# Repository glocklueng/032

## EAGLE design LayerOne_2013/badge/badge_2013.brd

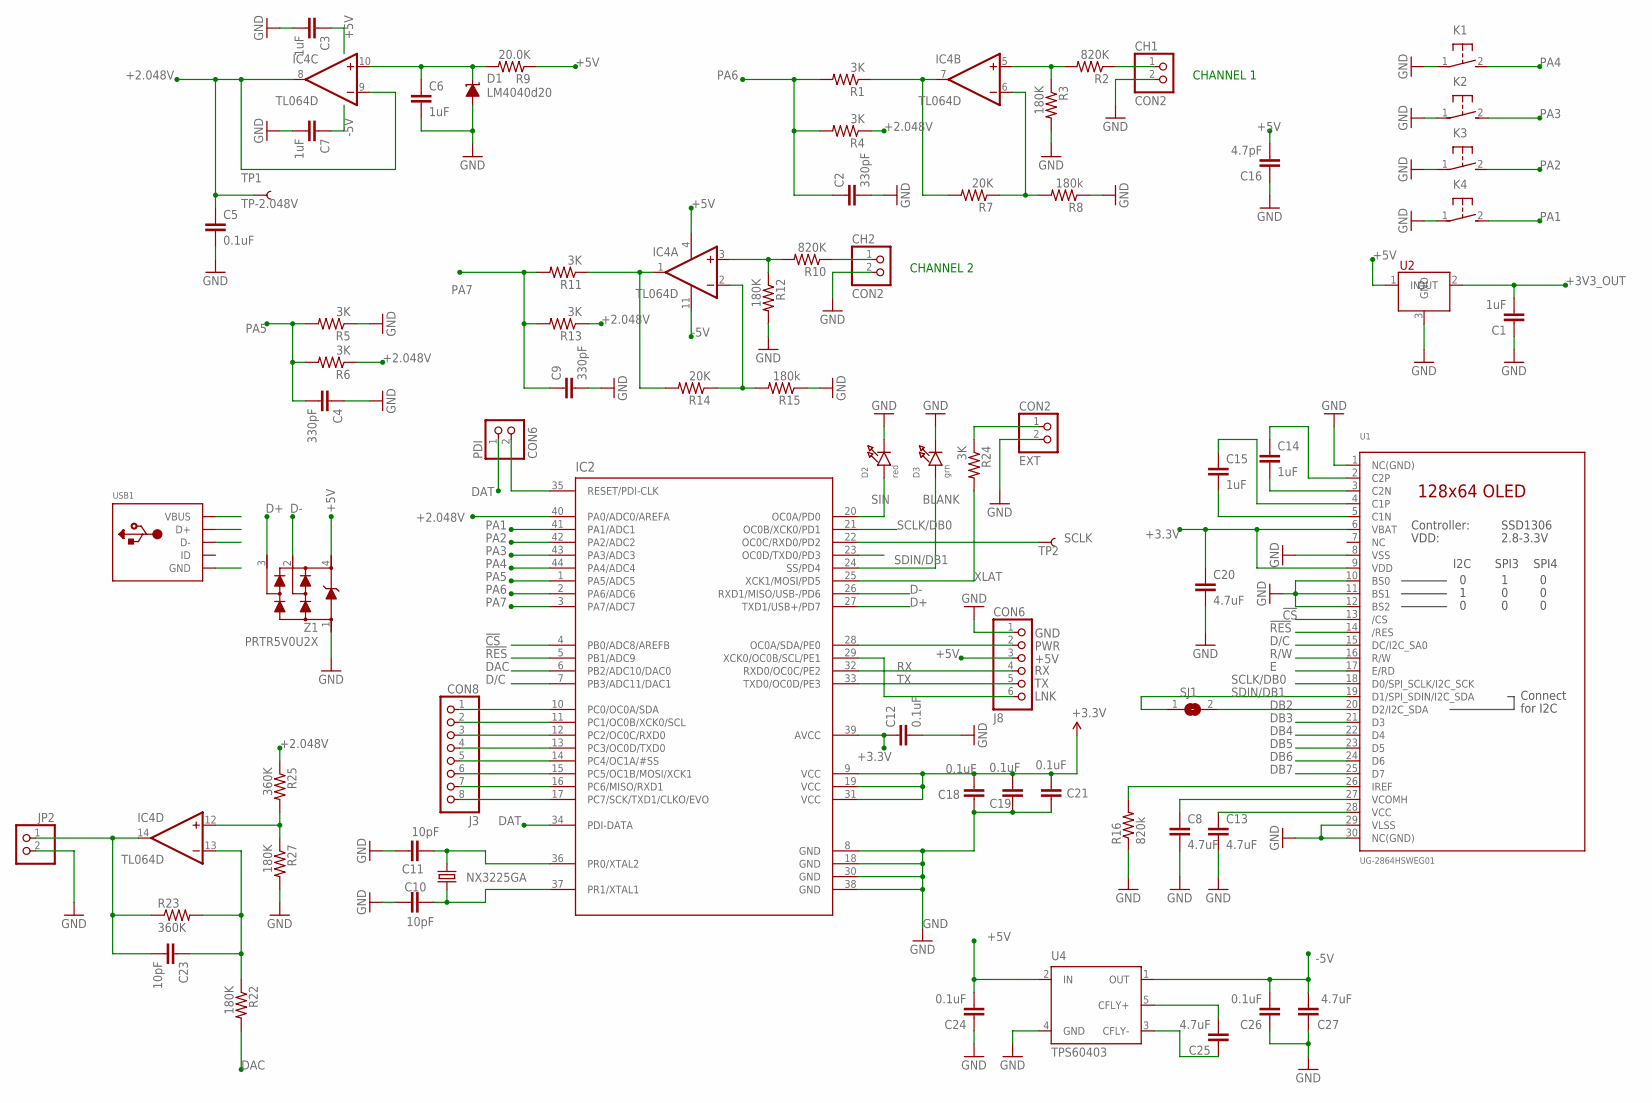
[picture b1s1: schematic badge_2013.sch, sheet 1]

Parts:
C1, C3, C6, C7, C14, C15: 1uF; 0805
C2, C4, C9: 330pF; 0805
C5, C12, C18, C19, C21, C24, C26: 0.1uF; 0805
C8, C13, C20, C25, C27: 4.7uF; 0805
C10, C11, C23: 10pF; 0805
C16: 4.7pF; 0805
CH1, CH2: CON2; 1X02_OVAL
CON2: EXT; 1X02_OVAL
CON6: J8; 1X06_OVAL
CON8: J3; 1X08_OVAL
D1: LM4040d20; DBZ_R-PDSO-G3
D2: red; CHIPLED_0805
D3: grn; CHIPLED_0805
IC2: NONOLITH_ATXMEGAXXA4U-AU; NONOLITH_TQFP-44
IC4: TL064D; SO14
JP2: HEADER-1X2; 1X02_OVAL
K1, K2, K3, K4: 5-XX; B3F-5XX
PDI: CON6; 1X02_OVAL
R1, R4, R5, R6, R11, R13, R24: 3K; R0805
R2, R10: 820K; R0805
R3, R12, R22, R27: 180K; R0805
R7, R14: 20K; R0805
R8, R15: 180k; R0805
R9: 20.0K; R0805
R16: 820k; R0805
R23, R25: 360K; R0805
SJ1: SOLDERJUMPERREFLOW; SOLDERJUMPER_REFLOW
TP1: TP-2.048V; PAD.02X.02
TP2: TEST-POINT2; PAD.02X.02
U1: UG-2864HSWEG01; MICROBUILDER_UG-2864HSWEG01_0.96IN_WRAPAROUND
U2: AP7333-33SOT23-3; SOT23-3
U4: TPS60403; SOT-23-5
USB1: USBMINIB; USB-MINIB
X2: NX3225GA
Z1: PRTR5V0U2X; SOT143B

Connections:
!CS: IC2.4 (PB0/ADC8/AREFB), U1.13 (/CS)
!RES: IC2.5 (PB1/ADC9), U1.14 (/RES)
+2.048V: C5.1, IC2.40 (PA0/ADC0/AREFA), IC4.8 (OUT), IC4.9 (-IN), R4.1, R6.1, R13.1, R25.1, TP1.P$1
+3.3V: C12.1, C18.2, C19.2, C20.1, C21.2, IC2.9 (VCC), IC2.19 (VCC), IC2.31 (VCC), IC2.39 (AVCC), U1.6 (VBAT), U1.9 (VDD); also elsewhere on the board
+3V3_OUT: C1.2, U2.2 (OUT); also elsewhere on the board
+5V: C3.1, C16.2, C24.2, CON6.3, IC4.4 (V+), R9.1, U2.1 (IN), U4.2 (IN), USB1.VBUS, Z1.4
-5V: C7.1, C26.2, C27.2, IC4.11 (V-), U4.1 (OUT)
BLANK: D3.A, IC2.24 (SS/PD4); also elsewhere on the board
D+: IC2.27 (TXD1/USB+/PD7), USB1.D+, Z1.3
D-: IC2.26 (RXD1/MISO/USB-/PD6), USB1.D-, Z1.2
D/C: IC2.7 (PB3/ADC11/DAC1), U1.15 (DC/I2C_SA0)
DAC: IC2.6 (PB2/ADC10/DAC0), R22.2
DAT: IC2.34 (PDI-DATA), PDI.1
DB2: SJ1.2, U1.20 (D2/I2C_SDA)
DB3: U1.21 (D3)
DB4: U1.22 (D4)
DB5: U1.23 (D5)
DB6: U1.24 (D6)
DB7: U1.25 (D7)
DGND: X2.2 (DGND), X2.4 (DGND)
E: U1.17 (E/RD)
GND: C1.1, C2.2, C3.2, C4.1, C5.2, C6.2, C7.2, C8.2, C9.2, C10.1, C11.1, C12.2, C13.2, C16.1, C18.1, C19.1, C20.2, C21.1, C24.1, C26.1, C27.1, CH1.2, CH2.2, CON2.2, CON6.1, D1.2 (A), D2.C, D3.C, IC2.8 (GND), IC2.18 (GND), IC2.30 (GND), IC2.38 (GND), JP2.2, K1.1, K2.1, K3.1, K4.1, R3.2, R5.1, R8.1, R12.2, R15.1, R16.1, R27.2, U1.1 (NC(GND)), U1.8 (VSS), U1.10 (BS0), U1.11 (BS1), U1.12 (BS2), U1.29 (VLSS), U1.30 (NC(GND)), U2.3 (GND), U4.4 (GND), USB1.GND, Z1.1; also elsewhere on the board
J3: CON8.5, IC2.14 (PC4/OC1A/#SS)
LNK: CON6.6, IC2.29 (XCK0/OC0B/SCL/PE1)
unnamed: C14.1, U1.2 (C2P)
unnamed: C14.2, U1.3 (C2N)
unnamed: C15.1, U1.4 (C1P)
unnamed: C15.2, U1.5 (C1N)
unnamed: CON2.1, R24.1
unnamed: C23.2, IC4.14 (OUT), JP2.1, R23.1
unnamed: C25.2, U4.5 (CFLY+)
unnamed: C25.1, U4.3 (CFLY-)
unnamed: CON8.1, IC2.10 (PC0/OC0A/SDA)
unnamed: CON8.2, IC2.11 (PC1/OC0B/XCK0/SCL)
unnamed: CON8.3, IC2.12 (PC2/OC0C/RXD0)
unnamed: CON8.4, IC2.13 (PC3/OC0D/TXD0)
unnamed: CON8.6, IC2.15 (PC5/OC1B/MOSI/XCK1)
unnamed: CON8.7, IC2.16 (PC6/MISO/RXD1)
unnamed: CON8.8, IC2.17 (PC7/SCK/TXD1/CLKO/EVO)
unnamed: IC4.12 (+IN), R25.2, R27.1
unnamed: C6.1, D1.1 (C), IC4.10 (+IN), R9.2
unnamed: C23.1, IC4.13 (-IN), R22.1, R23.2
unnamed: IC4.5 (+IN), R2.2, R3.1
unnamed: CH1.1, R2.1
unnamed: IC4.3 (+IN), R10.2, R12.1
unnamed: IC4.6 (-IN), R7.1, R8.2
unnamed: IC4.7 (OUT), R1.1, R7.2
unnamed: CH2.1, R10.1
unnamed: IC4.2 (-IN), R14.1, R15.2
unnamed: R16.2, U1.26 (IREF)
unnamed: C8.1, U1.27 (VCOMH)
unnamed: C13.1, U1.28 (VCC)
unnamed: IC4.1 (OUT), R11.1, R14.2
unnamed: C11.2, IC2.36 (PR0/XTAL2), X2.3 (2)
unnamed: C10.2, IC2.37 (PR1/XTAL1), X2.1
unnamed: IC2.35 (RESET/PDI-CLK), PDI.2
PA1: IC2.41 (PA1/ADC1), K4.2 (S)
PA2: IC2.42 (PA2/ADC2), K3.2 (S)
PA3: IC2.43 (PA3/ADC3), K2.2 (S)
PA4: IC2.44 (PA4/ADC4), K1.2 (S)
PA5: C4.2, IC2.1 (PA5/ADC5), R5.2, R6.2
PA6: C2.1, IC2.2 (PA6/ADC6), R1.2, R4.2
PA7: C9.1, IC2.3 (PA7/ADC7), R11.2, R13.2
PWR: CON6.2, IC2.28 (OC0A/SDA/PE0)
R/W: U1.16 (R/W)
RX: CON6.4, IC2.32 (RXD0/OC0C/PE2)
SCLK: IC2.22 (OC0C/RXD0/PD2), TP2.P$1; also elsewhere on the board
SCLK/DB0: IC2.21 (OC0B/XCK0/PD1), U1.18 (D0/SPI_SCLK/I2C_SCK)
SDIN/DB1: IC2.23 (OC0D/TXD0/PD3), SJ1.1, U1.19 (D1/SPI_SDIN/I2C_SDA)
SIN: D2.A, IC2.20 (OC0A/PD0); also elsewhere on the board
TX: CON6.5, IC2.33 (TXD0/OC0D/PE3)
XLAT: IC2.25 (XCK1/MOSI/PD5), R24.2; also elsewhere on the board

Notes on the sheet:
CHANNEL 1
CHANNEL 2

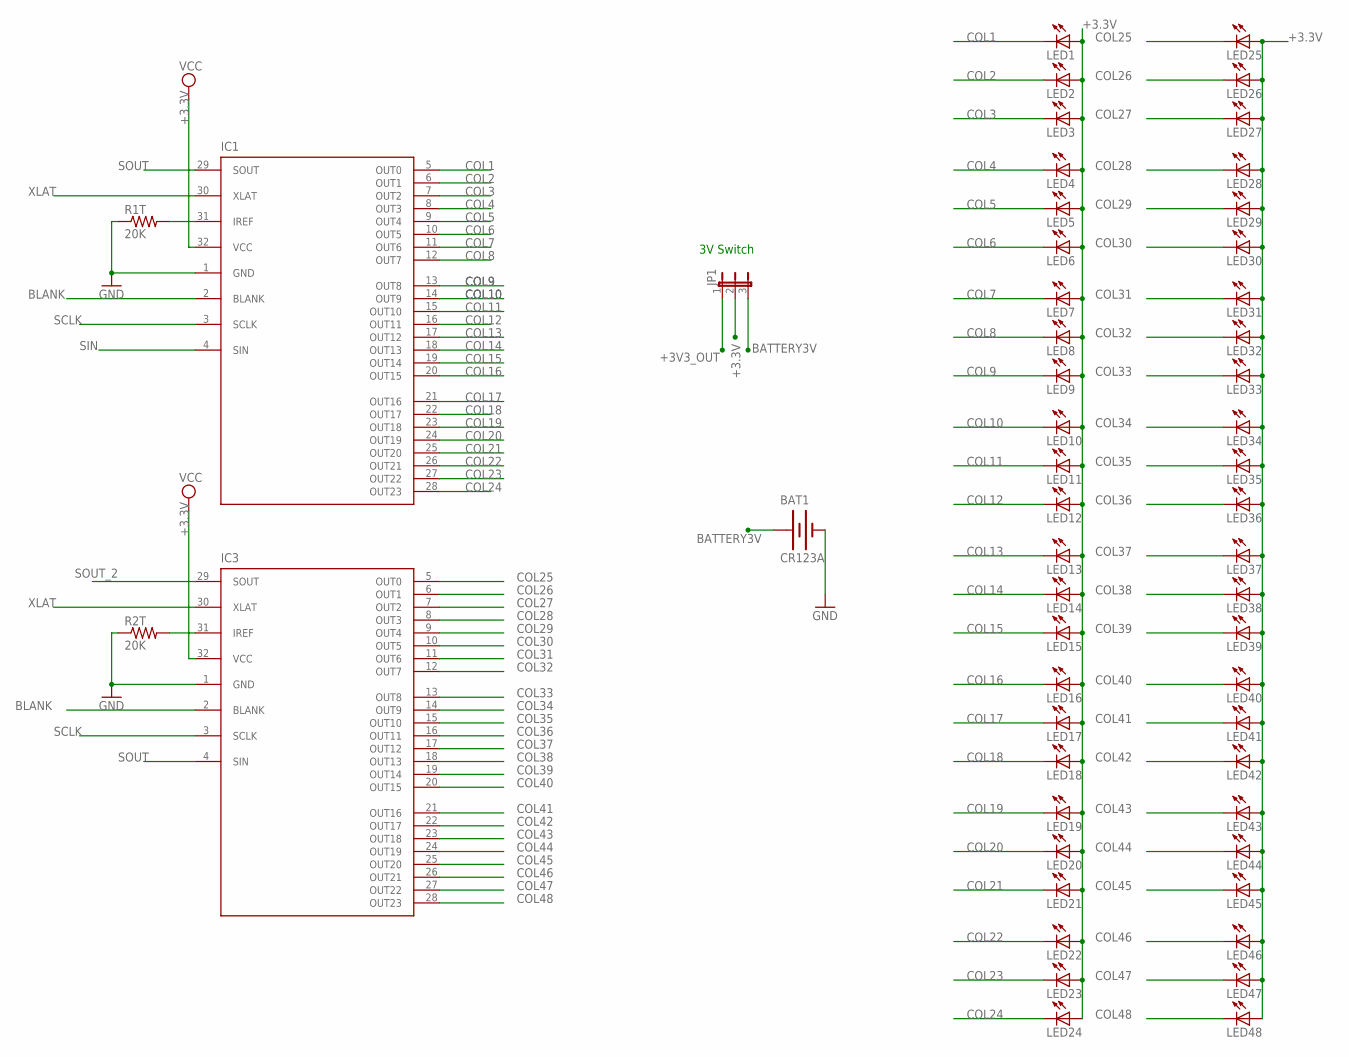
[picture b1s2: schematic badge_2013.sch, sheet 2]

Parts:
BAT1: CR123A; BATTERY_CR123A
IC1, IC3: SLICE_NOSHIFT_TLC5947HTSSOP32DAP; HTSSOP32DAP
JP1: JUMPER3
LED1, LED2, LED3, LED4, LED5, LED6, LED7, LED8, LED9, LED10, LED11, LED12, LED13, LED14, LED15, LED16, LED17, LED18, LED19, LED20, LED21, LED22, LED23, LED24, LED25, LED26, LED27, LED28, LED29, LED30, LED31, LED32, LED33, LED34, LED35, LED36, LED37, LED38, LED39, LED40, LED41, LED42, LED43, LED44, LED45, LED46, LED47, LED48: LED3MM
R1T, R2T: 20K; R0805

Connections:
+3.3V: IC1.32 (VCC), IC3.32 (VCC), JP1.2, LED1.A, LED2.A, LED3.A, LED4.A, LED5.A, LED6.A, LED7.A, LED8.A, LED9.A, LED10.A, LED11.A, LED12.A, LED13.A, LED14.A, LED15.A, LED16.A, LED17.A, LED18.A, LED19.A, LED20.A, LED21.A, LED22.A, LED23.A, LED24.A, LED25.A, LED26.A, LED27.A, LED28.A, LED29.A, LED30.A, LED31.A, LED32.A, LED33.A, LED34.A, LED35.A, LED36.A, LED37.A, LED38.A, LED39.A, LED40.A, LED41.A, LED42.A, LED43.A, LED44.A, LED45.A, LED46.A, LED47.A, LED48.A; also elsewhere on the board
+3V3_OUT: JP1.1; also elsewhere on the board
BATTERY3V: BAT1.+, JP1.3
BLANK: IC1.2 (BLANK), IC3.2 (BLANK); also elsewhere on the board
COL1: IC1.5 (OUT0), LED1.K (C)
COL2: IC1.6 (OUT1), LED2.K (C)
COL3: IC1.7 (OUT2), LED3.K (C)
COL4: IC1.8 (OUT3), LED4.K (C)
COL5: IC1.9 (OUT4), LED5.K (C)
COL6: IC1.10 (OUT5), LED6.K (C)
COL7: IC1.11 (OUT6), LED7.K (C)
COL8: IC1.12 (OUT7), LED8.K (C)
COL9: IC1.13 (OUT8), LED9.K (C)
COL10: IC1.14 (OUT9), LED10.K (C)
COL11: IC1.15 (OUT10), LED11.K (C)
COL12: IC1.16 (OUT11), LED12.K (C)
COL13: IC1.17 (OUT12), LED13.K (C)
COL14: IC1.18 (OUT13), LED14.K (C)
COL15: IC1.19 (OUT14), LED15.K (C)
COL16: IC1.20 (OUT15), LED16.K (C)
COL17: IC1.21 (OUT16), LED17.K (C)
COL18: IC1.22 (OUT17), LED18.K (C)
COL19: IC1.23 (OUT18), LED19.K (C)
COL20: IC1.24 (OUT19), LED20.K (C)
COL21: IC1.25 (OUT20), LED21.K (C)
COL22: IC1.26 (OUT21), LED22.K (C)
COL23: IC1.27 (OUT22), LED23.K (C)
COL24: IC1.28 (OUT23), LED24.K (C)
COL25: IC3.5 (OUT0), LED25.K (C)
COL26: IC3.6 (OUT1), LED26.K (C)
COL27: IC3.7 (OUT2), LED27.K (C)
COL28: IC3.8 (OUT3), LED28.K (C)
COL29: IC3.9 (OUT4), LED29.K (C)
COL30: IC3.10 (OUT5), LED30.K (C)
COL31: IC3.11 (OUT6), LED31.K (C)
COL32: IC3.12 (OUT7), LED32.K (C)
COL33: IC3.13 (OUT8), LED33.K (C)
COL34: IC3.14 (OUT9), LED34.K (C)
COL35: IC3.15 (OUT10), LED35.K (C)
COL36: IC3.16 (OUT11), LED36.K (C)
COL37: IC3.17 (OUT12), LED37.K (C)
COL38: IC3.18 (OUT13), LED38.K (C)
COL39: IC3.19 (OUT14), LED39.K (C)
COL40: IC3.20 (OUT15), LED40.K (C)
COL41: IC3.21 (OUT16), LED41.K (C)
COL42: IC3.22 (OUT17), LED42.K (C)
COL43: IC3.23 (OUT18), LED43.K (C)
COL44: IC3.24 (OUT19), LED44.K (C)
COL45: IC3.25 (OUT20), LED45.K (C)
COL46: IC3.26 (OUT21), LED46.K (C)
COL47: IC3.27 (OUT22), LED47.K (C)
COL48: IC3.28 (OUT23), LED48.K (C)
GND: BAT1.-, IC1.1 (GND), IC3.1 (GND), R1T.1, R2T.1; also elsewhere on the board
unnamed: IC3.31 (IREF), R2T.2
unnamed: IC1.31 (IREF), R1T.2
SCLK: IC1.3 (SCLK), IC3.3 (SCLK); also elsewhere on the board
SIN: IC1.4 (SIN); also elsewhere on the board
SOUT: IC1.29 (SOUT), IC3.4 (SIN)
SOUT_2: IC3.29 (SOUT)
XLAT: IC1.30 (XLAT), IC3.30 (XLAT); also elsewhere on the board

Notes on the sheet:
3V Switch

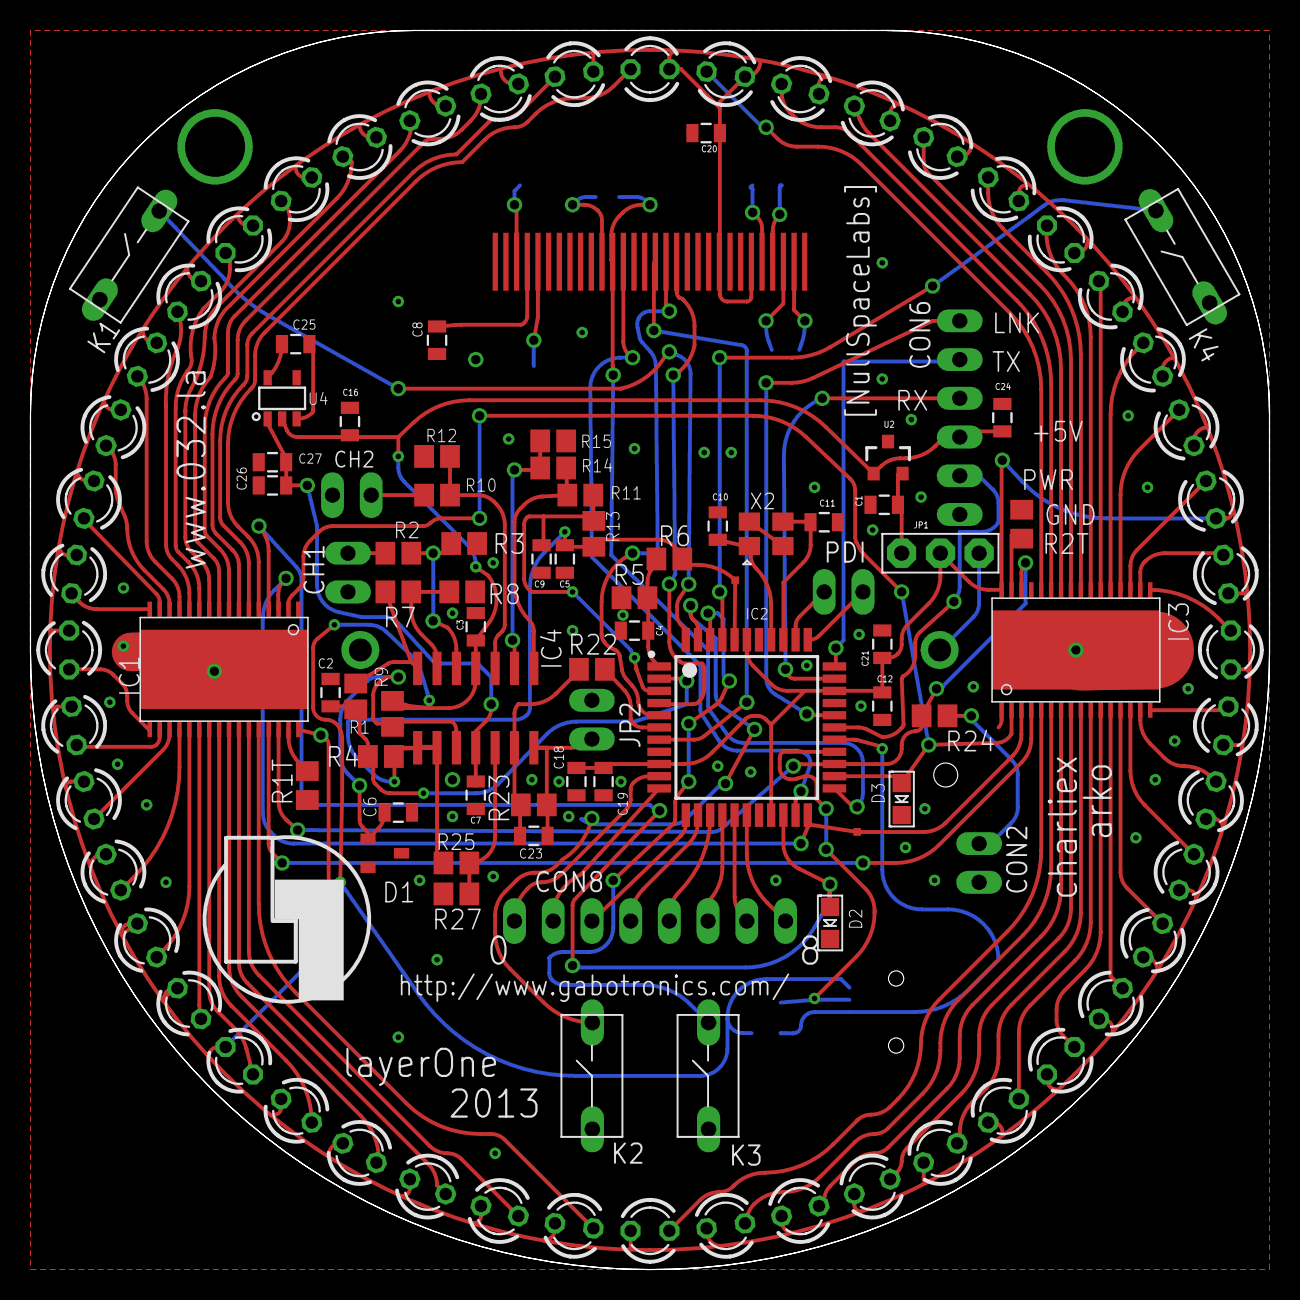
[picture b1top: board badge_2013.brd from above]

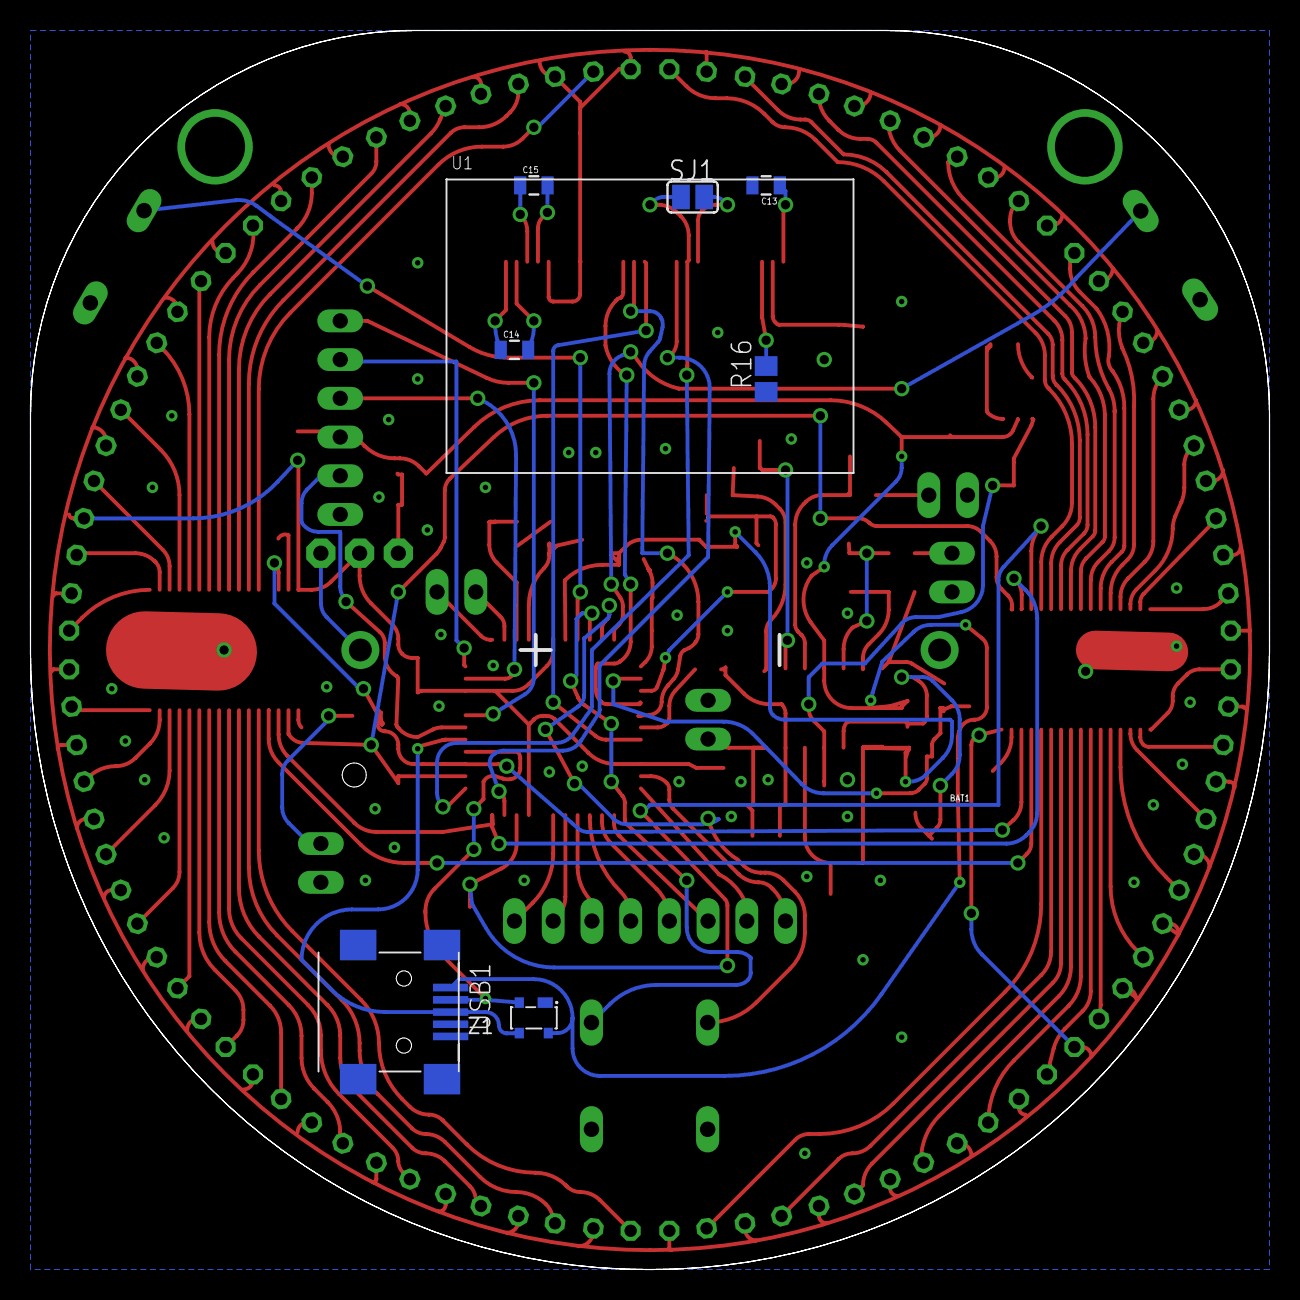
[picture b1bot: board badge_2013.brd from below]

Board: 2 copper layers, 81.3 x 81.3 mm, 125 parts (9 on the bottom side), 117 nets.

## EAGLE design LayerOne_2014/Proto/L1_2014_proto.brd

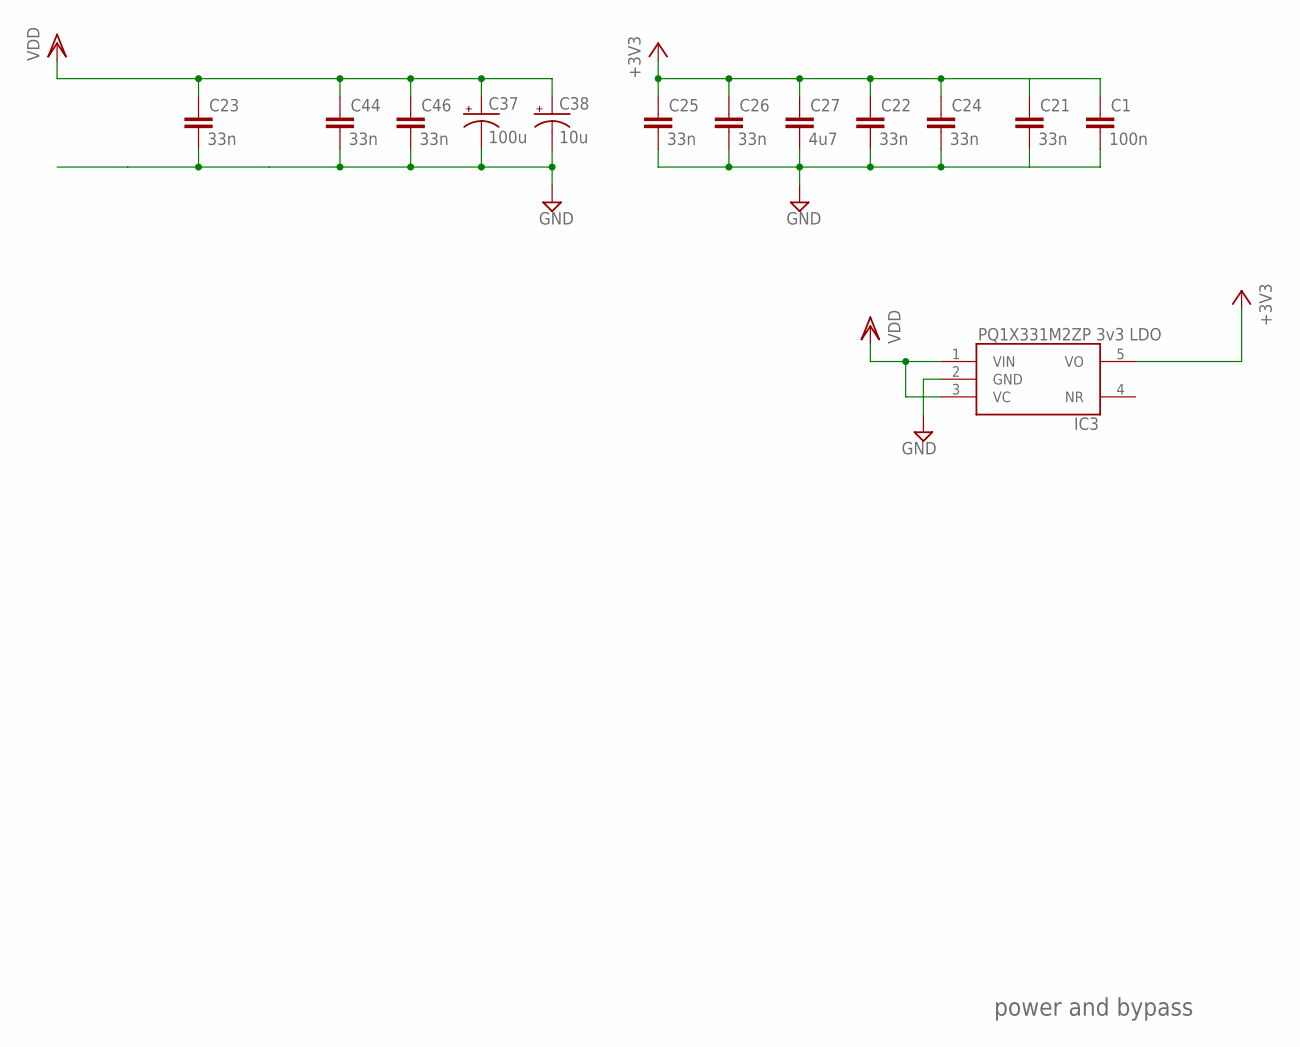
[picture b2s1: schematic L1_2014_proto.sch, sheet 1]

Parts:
C1: 100n; RLC_0603
C21, C22, C23, C24, C25, C26, C44, C46: 33n; RLC_0603
C27: 4u7; RLC_1210
C37: 100u; CAPCAITOR-ELECTROLYTIC-ALCHIP-MZA-F80
C38: 10u; CAPCAITOR-ELECTROLYTIC-ALCHIP-MZA-F80
IC3: PQ1X331M2ZP-3V3-LDO-SOT-23-5; SOT-23-5

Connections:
+3V3: C1.1, C21.1, C22.1, C24.1, C25.1, C26.1, C27.1, IC3.5 (VO); also elsewhere on the board
GND: C1.2, C21.2, C22.2, C23.2, C24.2, C25.2, C26.2, C27.2, C37.-, C38.-, C44.2, C46.2, IC3.2 (GND); also elsewhere on the board
VDD: C23.1, C37.+, C38.+, C44.1, C46.1, IC3.1 (VIN), IC3.3 (VC); also elsewhere on the board

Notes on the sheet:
power and bypass

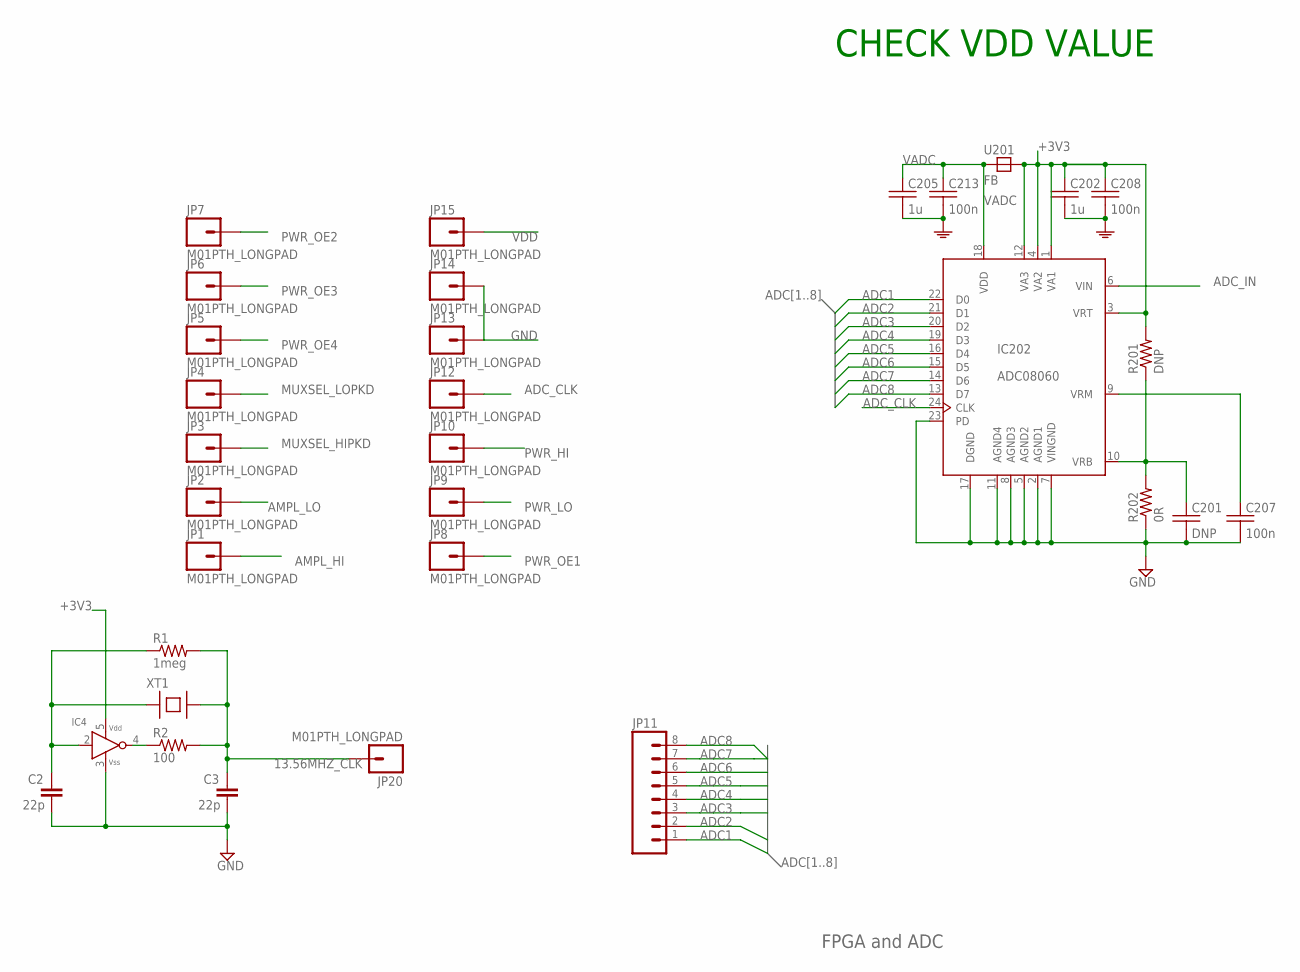
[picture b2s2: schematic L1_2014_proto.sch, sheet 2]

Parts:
C2, C3: 22p; RLC_0603
C201: DNP; 0603
C202, C205: 1u; 0603
C207, C208, C213: 100n; 0603
IC4: HCU-INVERTER; SMV-5
IC202: ADC08060; TSSOP24
JP1, JP2, JP3, JP4, JP5, JP6, JP7, JP8, JP9, JP10, JP12, JP13, JP14, JP15, JP20: M01PTH_LONGPAD; 1X01_LONGPAD
JP11: M08LONGPADS; 1X08_LONGPADS
R1: 1meg; RLC_0603
R2: 100; RLC_0603
R201: DNP; 0603
R202: 0R; 0603
U201: FB; 0805
XT1: XTAL-SMD-CITIZEN-CS10

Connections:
13.56MHZ_CLK: C3.1, JP20.1, R1.2, R2.2, XT1.B
+3V3: C202.1, C208.1, IC4.5 (VDD), IC202.1 (VA1), IC202.3 (VRT), IC202.4 (VA2), IC202.12 (VA3), R201.2, U201.2 (B); also elsewhere on the board
ADC1: IC202.22 (D0), JP11.1; also elsewhere on the board
ADC2: IC202.21 (D1), JP11.2; also elsewhere on the board
ADC3: IC202.20 (D2), JP11.3; also elsewhere on the board
ADC4: IC202.19 (D3), JP11.4; also elsewhere on the board
ADC5: IC202.16 (D4), JP11.5; also elsewhere on the board
ADC6: IC202.15 (D5), JP11.6; also elsewhere on the board
ADC7: IC202.14 (D6), JP11.7; also elsewhere on the board
ADC8: IC202.13 (D7), JP11.8; also elsewhere on the board
ADC_CLK: IC202.24 (CLK), JP12.1; also elsewhere on the board
ADC_IN: IC202.6 (VIN); also elsewhere on the board
AMPL_HI: JP1.1; also elsewhere on the board
AMPL_LO: JP2.1; also elsewhere on the board
GND: C2.2, C3.2, C201.2, C202.2, C205.2, C207.2, C208.2, C213.2, IC4.3 (VSS), IC202.2 (AGND1), IC202.5 (AGND2), IC202.7 (VINGND), IC202.8 (AGND3), IC202.11 (AGND4), IC202.17 (DGND), IC202.23 (PD), JP13.1, JP14.1, R202.1; also elsewhere on the board
MUXSEL_HIPKD: JP3.1; also elsewhere on the board
MUXSEL_LOPKD: JP4.1; also elsewhere on the board
unnamed: IC4.4 (Y), R2.1
unnamed: C2.1, IC4.2 (A), R1.1, XT1.A
unnamed: C201.1, IC202.10 (VRB), R201.1, R202.2
unnamed: C207.1, IC202.9 (VRM)
PWR_HI: JP10.1; also elsewhere on the board
PWR_LO: JP9.1; also elsewhere on the board
PWR_OE1: JP8.1; also elsewhere on the board
PWR_OE2: JP7.1; also elsewhere on the board
PWR_OE3: JP6.1; also elsewhere on the board
PWR_OE4: JP5.1; also elsewhere on the board
VADC: C205.1, C213.1, IC202.18 (VDD), U201.1 (A)
VDD: JP15.1; also elsewhere on the board

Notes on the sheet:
FPGA and ADC
CHECK VDD VALUE

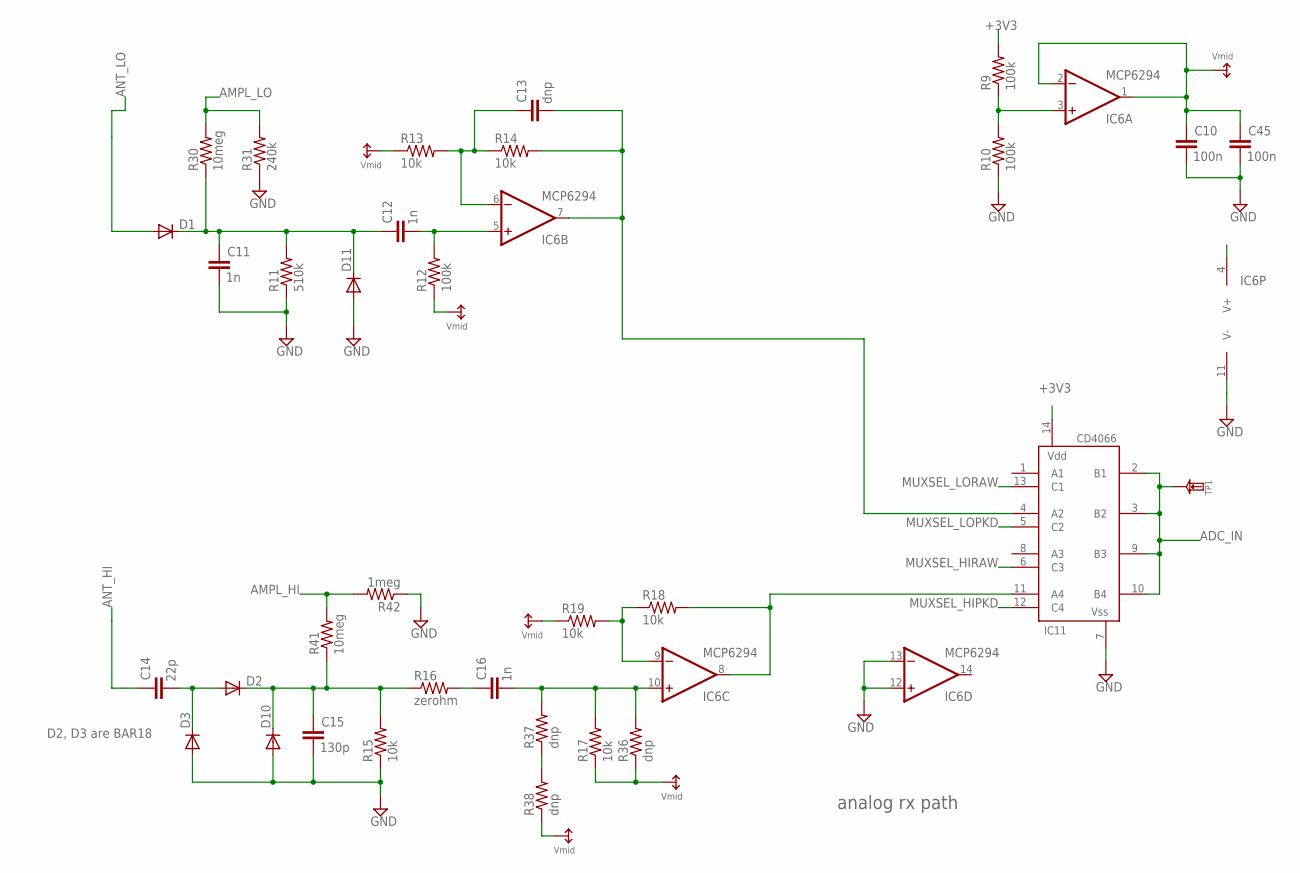
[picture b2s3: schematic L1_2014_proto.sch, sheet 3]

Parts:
C10, C45: 100n; RLC_0603
C11, C12, C16: 1n; RLC_0603
C13: dnp; RLC_0603
C14: 22p; RLC_0603
C15: 130p; RLC_0603
D1, D2, D3, D10, D11: DIODE-SMD-SOT23; SOT23-3LEAD
IC6: MCP6294; TSSOP-14
IC11: CD4066; TSSOP-14
R9, R10, R12: 100k; RLC_0603
R11: 510k; RLC_0603
R13, R14, R15, R17, R18, R19: 10k; RLC_0603
R16: zerohm; RLC_0603
R30, R41: 10meg; RLC_0603
R31: 240k; RLC_0603
R36, R37, R38: dnp; RLC_0603
R42: 1meg; RLC_0603
TP1: TESTPADKEYSTONE-SMD; KEYSTONE-SMD-TESTPOINT-5015

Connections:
+3V3: IC6.4 (V+), IC11.14 (VDD), R9.2; also elsewhere on the board
ADCDR_HI: IC6.8 (OUT), IC11.11 (A4), R18.2
ADCDR_LO: C13.2, IC6.7 (OUT), IC11.4 (A2), R14.2
ADC_IN: IC11.2 (B1), IC11.3 (B2), IC11.9 (B3), IC11.10 (B4), TP1.1; also elsewhere on the board
AMPL_HI: R41.2, R42.2; also elsewhere on the board
AMPL_LO: R30.2, R31.2; also elsewhere on the board
ANT_HI: C14.1; also elsewhere on the board
ANT_LO: D1.1 (A); also elsewhere on the board
GND: C10.2, C11.2, C15.2, C45.2, D3.1 (A), D10.1 (A), D11.1 (A), IC6.11 (V-), IC6.12 (+IN), IC6.13 (-IN), IC11.7 (VSS), R10.1, R11.1, R15.1, R31.1, R42.1; also elsewhere on the board
MUXSEL_HIPKD: IC11.12 (C4); also elsewhere on the board
MUXSEL_HIRAW: IC11.6 (C3)
MUXSEL_LOPKD: IC11.5 (C2); also elsewhere on the board
MUXSEL_LORAW: IC11.13 (C1)
unnamed: IC6.3 (+IN), R9.1, R10.2
unnamed: IC6.9 (-IN), R18.1, R19.2
unnamed: C12.2, IC6.5 (+IN), R12.2
unnamed: C13.1, IC6.6 (-IN), R13.2, R14.1
unnamed: C16.1, R16.2
unnamed: C11.1, C12.1, D1.3 (C), D11.3 (C), R11.2, R30.1
unnamed: C14.2, D2.1 (A), D3.3 (C)
unnamed: C15.1, D2.3 (C), D10.3 (C), R15.2, R16.1, R41.1
unnamed: C16.2, IC6.10 (+IN), R17.2, R36.2, R37.2
unnamed: R37.1, R38.2
VMID: C10.1, C45.1, IC6.1 (OUT), IC6.2 (-IN), R12.1, R13.1, R17.1, R19.1, R36.1, R38.1

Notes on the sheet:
analog rx path
D2, D3 are BAR18

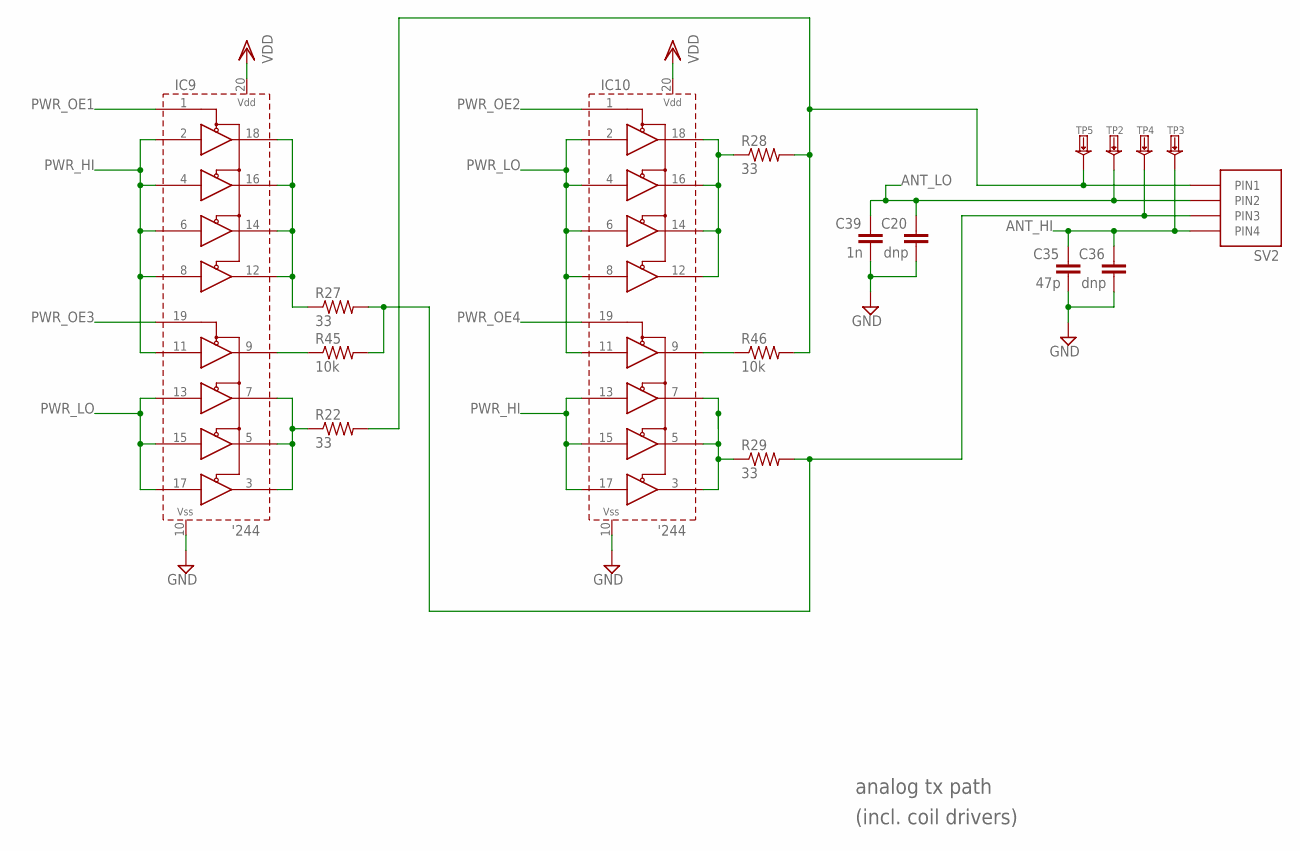
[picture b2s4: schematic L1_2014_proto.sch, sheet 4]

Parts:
C20, C36: dnp; RLC_0603
C35: 47p; RLC_0603
C39: 1n; RLC_0603
IC9, IC10: 74XX244-OCTAL-TRISTATE-BUFFERS; TSSOP-20
R22, R27, R28, R29: 33; RLC_0603
R45, R46: 10k; RLC_0603
SV2: HIROSE-MQ172-4POS
TP2, TP3, TP4, TP5: TESTPADKEYSTONE-SMD; KEYSTONE-SMD-TESTPOINT-5015

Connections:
ANT_HI: C35.1, C36.1, SV2.4 (PIN4), TP3.1; also elsewhere on the board
ANT_LO: C20.1, C39.1, SV2.2 (PIN2), TP2.1; also elsewhere on the board
GND: C20.2, C35.2, C36.2, C39.2, IC9.10 (VSS), IC10.10 (VSS); also elsewhere on the board
unnamed: R27.2, R29.2, R45.2, SV2.3 (PIN3), TP4.1
unnamed: R22.2, R28.2, R46.2, SV2.1 (PIN1), TP5.1
unnamed: IC9.12 (1Y4), IC9.14 (1Y3), IC9.16 (1Y2), IC9.18 (1Y1), R27.1
unnamed: IC10.12 (1Y4), IC10.14 (1Y3), IC10.16 (1Y2), IC10.18 (1Y1), R28.1
unnamed: IC9.3 (2Y4), IC9.5 (2Y3), IC9.7 (2Y2), R22.1
unnamed: IC10.3 (2Y4), IC10.5 (2Y3), IC10.7 (2Y2), R29.1
unnamed: IC9.9 (2Y1), R45.1
unnamed: IC10.9 (2Y1), R46.1
PWR_HI: IC9.2 (1A1), IC9.4 (1A2), IC9.6 (1A3), IC9.8 (1A4), IC9.11 (2A1), IC10.13 (2A2), IC10.15 (2A3), IC10.17 (2A4); also elsewhere on the board
PWR_LO: IC9.13 (2A2), IC9.15 (2A3), IC9.17 (2A4), IC10.2 (1A1), IC10.4 (1A2), IC10.6 (1A3), IC10.8 (1A4), IC10.11 (2A1); also elsewhere on the board
PWR_OE1: IC9.1 (1NOE); also elsewhere on the board
PWR_OE2: IC10.1 (1NOE); also elsewhere on the board
PWR_OE3: IC9.19 (2NOE); also elsewhere on the board
PWR_OE4: IC10.19 (2NOE); also elsewhere on the board
VDD: IC9.20 (VDD), IC10.20 (VDD); also elsewhere on the board

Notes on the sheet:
analog tx path
(incl. coil drivers)

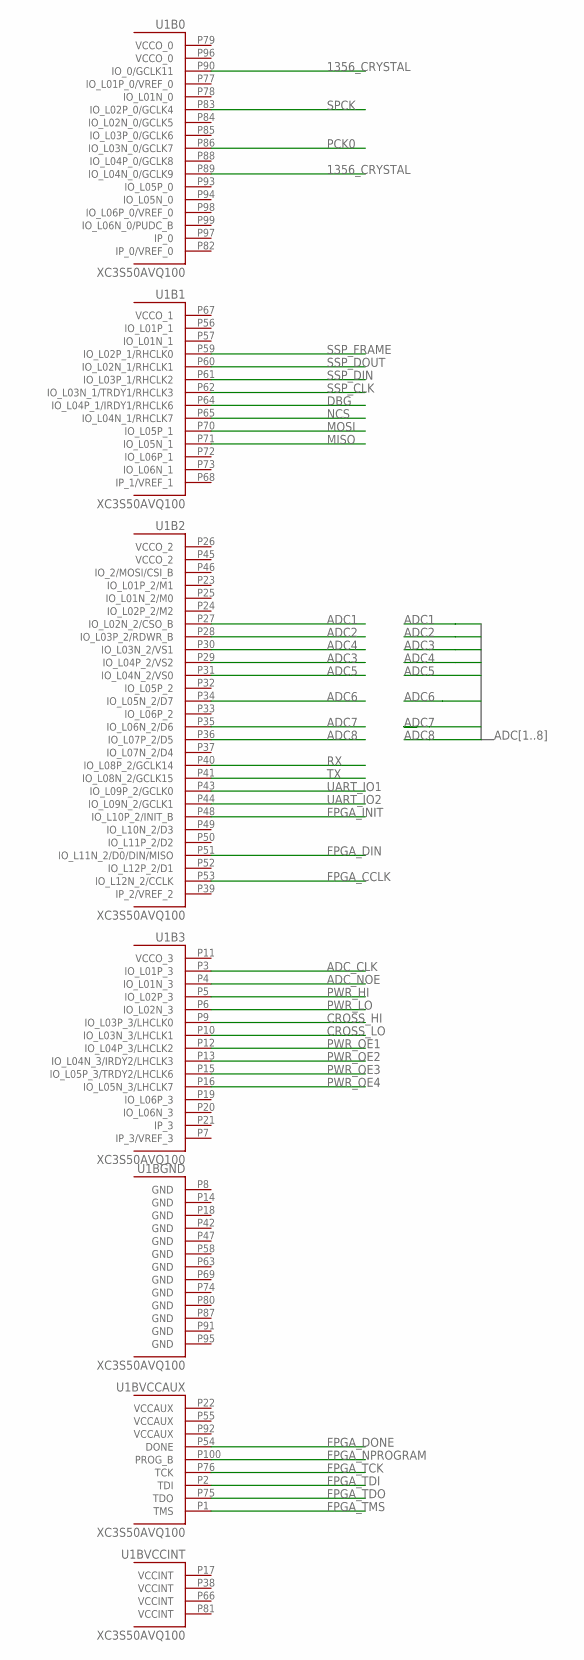
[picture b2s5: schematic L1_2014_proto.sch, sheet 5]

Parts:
U1: XC3S50AVQ100; VQ100

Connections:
1356_CRYSTAL: U1.P89 (IO_L04N_0/GCLK9), U1.P90 (IO_0/GCLK11)
ADC1: U1.P27 (IO_L02N_2/CSO_B); also elsewhere on the board
ADC2: U1.P28 (IO_L03P_2/RDWR_B); also elsewhere on the board
ADC3: U1.P29 (IO_L04P_2/VS2); also elsewhere on the board
ADC4: U1.P30 (IO_L03N_2/VS1); also elsewhere on the board
ADC5: U1.P31 (IO_L04N_2/VS0); also elsewhere on the board
ADC6: U1.P34 (IO_L05N_2/D7); also elsewhere on the board
ADC7: U1.P35 (IO_L06N_2/D6); also elsewhere on the board
ADC8: U1.P36 (IO_L07P_2/D5); also elsewhere on the board
ADC_CLK: U1.P3 (IO_L01P_3); also elsewhere on the board
ADC_NOE: U1.P4 (IO_L01N_3)
CROSS_HI: U1.P9 (IO_L03P_3/LHCLK0)
CROSS_LO: U1.P10 (IO_L03N_3/LHCLK1)
DBG: U1.P64 (IO_L04P_1/IRDY1/RHCLK6)
FPGA_CCLK: U1.P53 (IO_L12N_2/CCLK)
FPGA_DIN: U1.P51 (IO_L11N_2/D0/DIN/MISO)
FPGA_DONE: U1.P54 (DONE)
FPGA_INIT: U1.P48 (IO_L10P_2/INIT_B)
FPGA_NPROGRAM: U1.P100 (PROG_B)
FPGA_TCK: U1.P76 (TCK)
FPGA_TDI: U1.P2 (TDI)
FPGA_TDO: U1.P75 (TDO)
FPGA_TMS: U1.P1 (TMS)
GND: U1.P8 (GND), U1.P14 (GND), U1.P18 (GND), U1.P42 (GND), U1.P47 (GND), U1.P58 (GND), U1.P63 (GND), U1.P69 (GND), U1.P74 (GND), U1.P80 (GND), U1.P87 (GND), U1.P91 (GND), U1.P95 (GND); also elsewhere on the board
MISO: U1.P71 (IO_L05N_1)
MOSI: U1.P70 (IO_L05P_1)
NCS: U1.P65 (IO_L04N_1/RHCLK7)
PCK0: U1.P86 (IO_L03N_0/GCLK7)
PWR_HI: U1.P5 (IO_L02P_3); also elsewhere on the board
PWR_LO: U1.P6 (IO_L02N_3); also elsewhere on the board
PWR_OE1: U1.P12 (IO_L04P_3/LHCLK2); also elsewhere on the board
PWR_OE2: U1.P13 (IO_L04N_3/IRDY2/LHCLK3); also elsewhere on the board
PWR_OE3: U1.P15 (IO_L05P_3/TRDY2/LHCLK6); also elsewhere on the board
PWR_OE4: U1.P16 (IO_L05N_3/LHCLK7); also elsewhere on the board
RX: U1.P40 (IO_L08P_2/GCLK14)
SPCK: U1.P83 (IO_L02P_0/GCLK4)
SSP_CLK: U1.P62 (IO_L03N_1/TRDY1/RHCLK3)
SSP_DIN: U1.P61 (IO_L03P_1/RHCLK2)
SSP_DOUT: U1.P60 (IO_L02N_1/RHCLK1)
SSP_FRAME: U1.P59 (IO_L02P_1/RHCLK0)
TX: U1.P41 (IO_L08N_2/GCLK15)
UART_IO1: U1.P43 (IO_L09P_2/GCLK0)
UART_IO2: U1.P44 (IO_L09N_2/GCLK1)

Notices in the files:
parts and their libraries:
SparkFun-Electromechanical: Licensing: CC v3.0 Share-Alike You are welcome to use this library for commercial purposes.
microbuilder: This work is placed in the public domain, and may be freely used for commercial and non-commercial work with the following conditions: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
